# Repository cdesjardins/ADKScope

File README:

I want to build a logic analyzer from the following parts:
Ardunio mega ADK
Arduino mega shield
Flashy capture card (knjn.com)
Android phone for display

But the mega shield isn't very good for anything because it is just a bunch of holes...
In order to use it for anything you have to soldier blob everywhere, which I don't like.
So I intend to fix it.

To see the shield check out this image:
https://github.com/cdesjardins/ADKScope/blob/master/megashield/ADKScopeShield.png

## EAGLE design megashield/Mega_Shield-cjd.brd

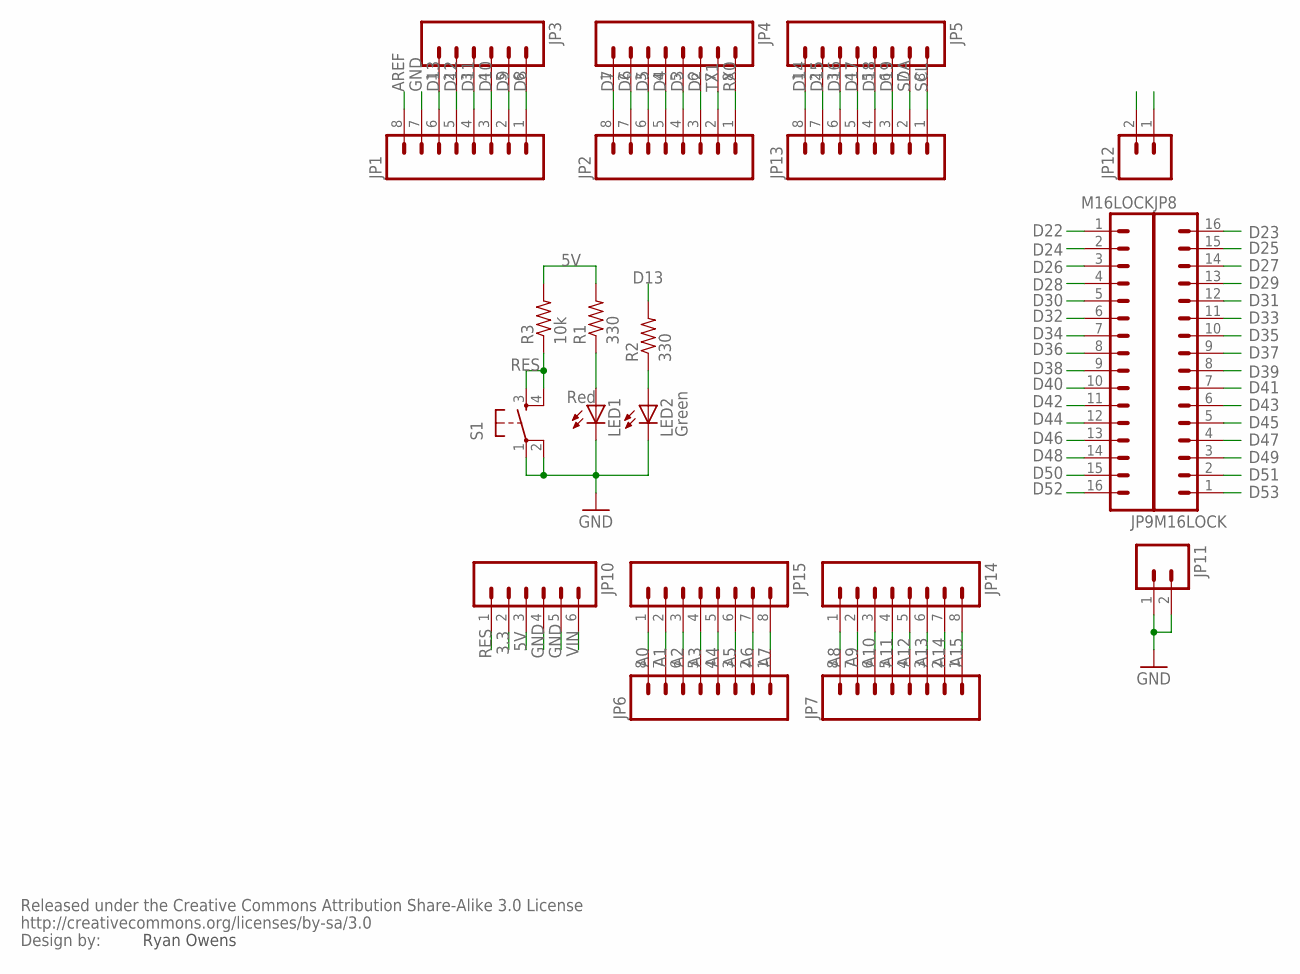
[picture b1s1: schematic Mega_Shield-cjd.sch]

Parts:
JP1, JP2, JP13, JP14, JP15: M081X08_LOCK_NO_PIN1; 1X08_LOCK_NO_PIN1
JP3: M06NO_SILK_FEMALE_PTH; 1X06_NO_SILK
JP4, JP5, JP6, JP7: M08NO_SILK_FEMALE_PTH; 1X08_NO_SILK
JP8, JP9: M16LOCK; 1X16_LOCK
JP10: M06LOCK; 1X06_LOCK
JP11, JP12: M02LOCK; 1X02_LOCK
LED1: Red; LED5MM
LED2: Green; LED5MM
R1, R2: 330; AXIAL-0.3
R3: 10k; AXIAL-0.3
S1: TAC_SWITCHPTH; TACTILE-PTH
U$2: CREATIVE_COMMONS

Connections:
3.3: JP10.2
5V: JP10.3, R1.P$2 (2), R3.P$2 (2)
5V@1: JP12.1, JP12.2
A0: JP6.8, JP15.1
A1: JP6.7, JP15.2
A2: JP6.6, JP15.3
A3: JP6.5, JP15.4
A4: JP6.4, JP15.5
A5: JP6.3, JP15.6
A6: JP6.2, JP15.7
A7: JP6.1, JP15.8
A8: JP7.8, JP14.1
A9: JP7.7, JP14.2
A10: JP7.6, JP14.3
A11: JP7.5, JP14.4
A12: JP7.4, JP14.5
A13: JP7.3, JP14.6
A14: JP7.2, JP14.7
A15: JP7.1, JP14.8
AREF: JP1.8
D2: JP2.3, JP4.6
D3: JP2.4, JP4.5
D4: JP2.5, JP4.4
D5: JP2.6, JP4.3
D6: JP2.7, JP4.2
D7: JP2.8, JP4.1
D8: JP1.1, JP3.6
D9: JP1.2, JP3.5
D10: JP1.3, JP3.4
D11: JP1.4, JP3.3
D12: JP1.5, JP3.2
D13: JP1.6, JP3.1, R2.P$2 (2)
D14: JP5.1, JP13.8
D15: JP5.2, JP13.7
D16: JP5.3, JP13.6
D17: JP5.4, JP13.5
D18: JP5.5, JP13.4
D19: JP5.6, JP13.3
D22: JP9.1
D23: JP8.16
D24: JP9.2
D25: JP8.15
D26: JP9.3
D27: JP8.14
D28: JP9.4
D29: JP8.13
D30: JP9.5
D31: JP8.12
D32: JP9.6
D33: JP8.11
D34: JP9.7
D35: JP8.10
D36: JP9.8
D37: JP8.9
D38: JP9.9
D39: JP8.8
D40: JP9.10
D41: JP8.7
D42: JP9.11
D43: JP8.6
D44: JP9.12
D45: JP8.5
D46: JP9.13
D47: JP8.4
D48: JP9.14
D49: JP8.3
D50: JP9.15
D51: JP8.2
D52: JP9.16
D53: JP8.1
GND: JP1.7, JP10.4, JP10.5, JP11.1, JP11.2, LED1.K (C), LED2.K (C), S1.1, S1.2
unnamed: LED1.A, R1.P$1 (1)
unnamed: LED2.A, R2.P$1 (1)
RES: JP10.1, R3.P$1 (1), S1.3, S1.4
RX0: JP2.1, JP4.8
SCL: JP5.8, JP13.1
SDA: JP5.7, JP13.2
TX1: JP2.2, JP4.7
VIN: JP10.6

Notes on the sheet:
Ryan Owens

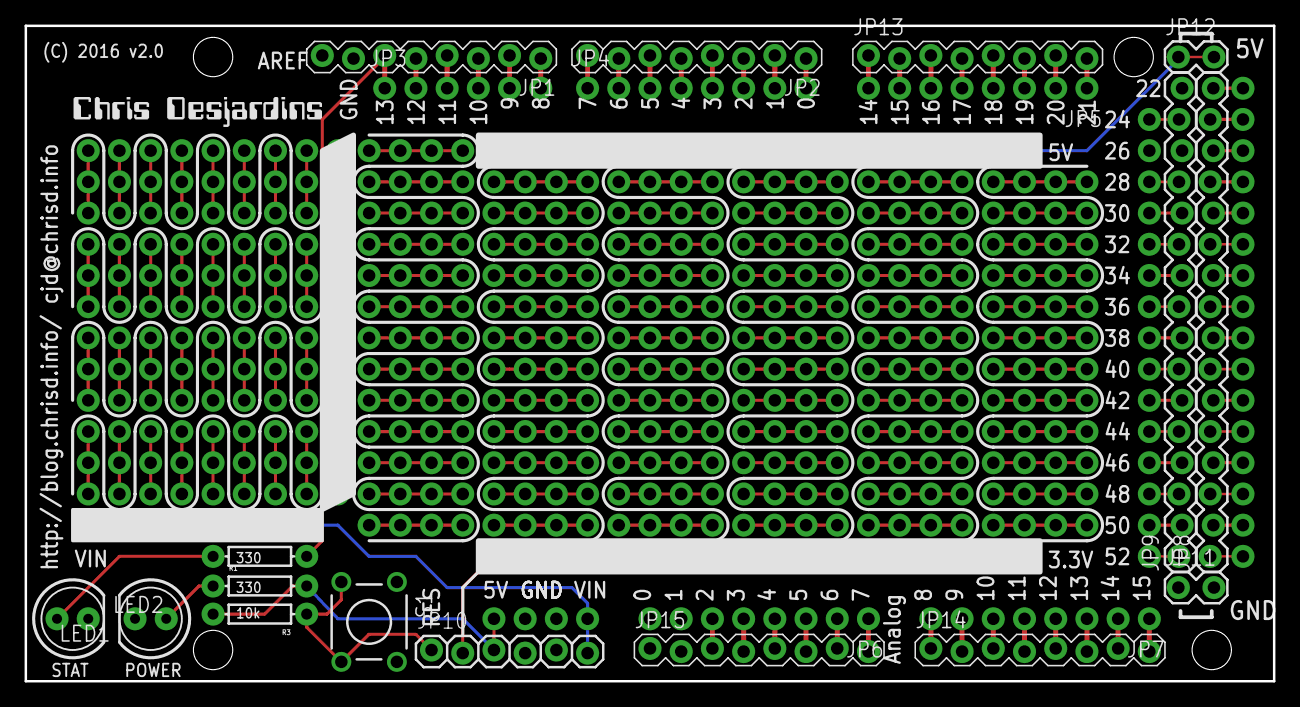
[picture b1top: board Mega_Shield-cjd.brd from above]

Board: 2 copper layers, 101.6 x 53.3 mm, 24 parts (1 on the bottom side), 44 nets.

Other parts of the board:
U$1: LOGO
U$3: OSHW2

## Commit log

2012-03-07 Adding initial version of the mega sheild from sparkfun.
2012-03-07 Add readme
2012-03-07 First pass done...
2012-03-08 Rework dir structure
2012-03-08 Major changes to the layout...
2012-03-08 Updates to board
2012-03-27 Adding arduino code to read the data capture card
2012-03-27 Minor updates to the layout, added an image
2012-03-27 Change the filenames
2012-12-08 Change readme
2012-12-08 removed jpg
2012-12-29 Starting USB interface work...
2012-12-29 Adding ADK support...
2012-12-30 Add build instructions to makefile, and correct filename.
2012-12-30 Adding first non-working pass of scopedroid
2012-12-30 Initial graph is shown
2016-01-19 Update with larger busses
2016-01-19 Add silkscreen to the bottom
2016-01-27 Add OSHW logo
2016-02-06 Update image

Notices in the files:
megashield/Mega_Shield-cjd.brd:
(C) 2016 v2.0
parts and their libraries:
SparkFun: Released under the Creative Commons Attribution Share-Alike 3.0 License
SparkFun: http://creativecommons.org/licenses/by-sa/3.0
SparkFun-Connectors: Licensing: Creative Commons ShareAlike 4.0 International - https://creativecommons.org/licenses/by-sa/4.0
